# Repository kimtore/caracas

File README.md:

# Caracas

Caracas is an open source DIY car stereo system for the Toyota Avensis 2007, running on Raspberry Pi with custom hardware modifications.

[See pictures](http://imgur.com/a/6FCoq) of Caracas in action!

## Features

* Front panel with volume button and a 800x480 resistive touch panel with backlight control.
* Control music and other functions using steering wheel control buttons.
* Ignition key detection: hardware controlled power-on, software-controlled power-off.
* Plays music using MPD, through a HIFImeDIY Sabre DAC ES9023 to a class D 400W RMS amplifier.
* ISO 10487 connection for power and speaker connections.
* Custom-designed Raspberry Pi HAT for interfacing with the car hardware.
* SSD disk stores huge amounts of music.
* 4G Internet connection using car antenna.
* GPS module using car antenna.
* Custom interface with music controls, using Qt.
* ~~World-wide road navigation using Marble and OpenStreetMap.~~

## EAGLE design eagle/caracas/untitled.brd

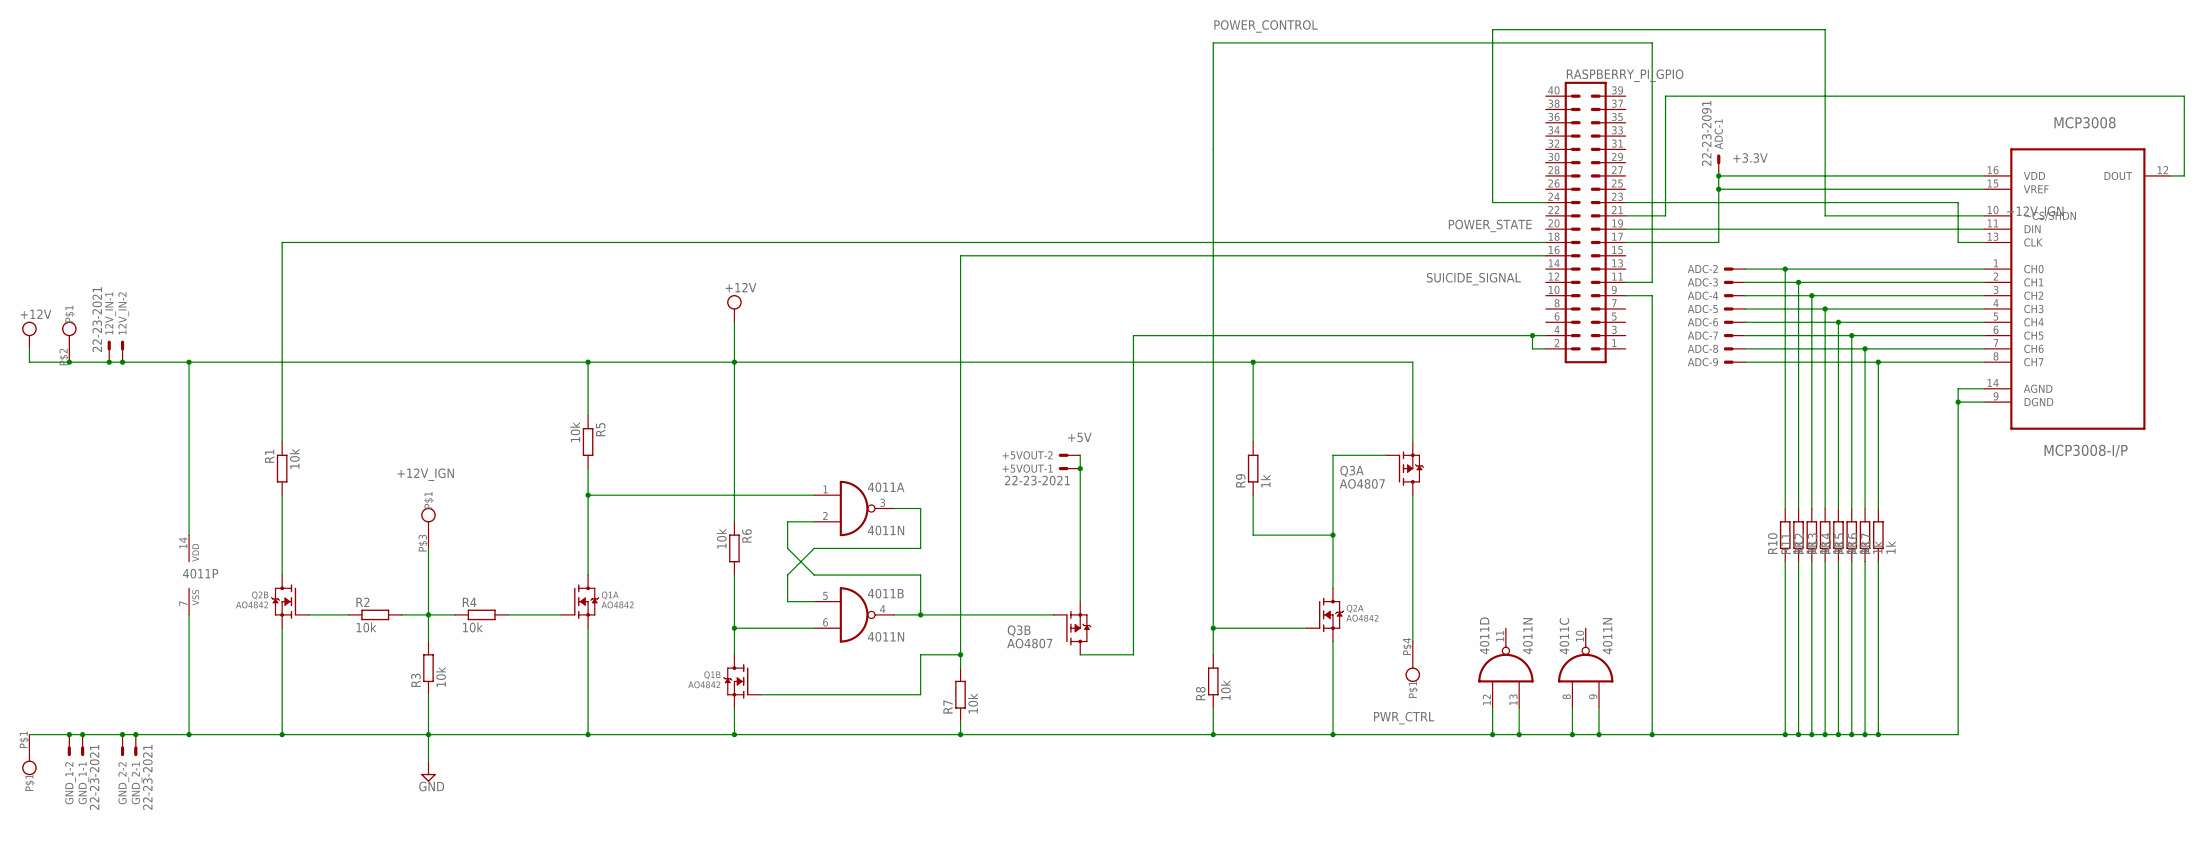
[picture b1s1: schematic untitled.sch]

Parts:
12V_IN: 22-23-2021
4011: 4011N; DIL14
+5VOUT: 22-23-2021
ADC: 22-23-2091
EXT: MKDS3
GND_1, GND_2: 22-23-2021
MCP3008: MCP3008-I/P; DIP254P762X432-16
Q1, Q2: AO4842; 8-SOIC
Q3: AO4807; 8-SOIC
R1, R2, R3, R4, R5, R6, R7, R8: 10k; 0207/10
R9, R10, R11, R12, R13, R14, R15, R16, R17: 1k; 0207/10
RASPBERRY_PI_GPIO: MA20-2

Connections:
+3.3V: ADC.1, MCP3008.15 (VREF), MCP3008.16 (VDD), RASPBERRY_PI_GPIO.17
+5V: +5VOUT.1, +5VOUT.2, Q3.P$1 (S)
+12V_IGN: EXT.P$3, R2.2, R3.2, R4.1
ANA_0: ADC.2, MCP3008.1 (CH0), R10.2
ANA_1: ADC.3, MCP3008.2 (CH1), R11.2
GND@BOTTOM: 4011.7 (VSS), 4011.8 (I0), 4011.9 (I1), 4011.12 (I0), 4011.13 (I1), EXT.P$1, GND_1.1, GND_1.2, GND_2.1, GND_2.2, MCP3008.9 (DGND), MCP3008.14 (AGND), Q1.P$1 (S), Q1.P$3 (S), Q2.P$1 (S), Q2.P$3 (S), R3.1, R7.1, R8.1, R10.1, R11.1, R12.1, R13.1, R14.1, R15.1, R16.1, R17.1, RASPBERRY_PI_GPIO.9
MOSFET_ON: 4011.2 (I1), 4011.4 (O), Q3.P$2 (G)
unnamed: 4011.3 (O), 4011.5 (I0)
unnamed: 4011.6 (I1), Q1.P$7 (D), Q1.P$8 (D), R6.2
unnamed: MCP3008.13 (CLK), RASPBERRY_PI_GPIO.23
unnamed: MCP3008.12 (DOUT), RASPBERRY_PI_GPIO.21
unnamed: MCP3008.11 (DIN), RASPBERRY_PI_GPIO.19
unnamed: ADC.4, MCP3008.3 (CH2), R12.2
unnamed: ADC.5, MCP3008.4 (CH3), R13.2
unnamed: ADC.6, MCP3008.5 (CH4), R14.2
unnamed: ADC.7, MCP3008.6 (CH5), R15.2
unnamed: 4011.1 (I0), Q1.P$5 (D), Q1.P$6 (D), R5.2
unnamed: Q1.P$4 (G), R4.2
unnamed: MCP3008.10 (~CS/SHDN), RASPBERRY_PI_GPIO.24
unnamed: ADC.8, MCP3008.7 (CH6), R16.2
unnamed: ADC.9, MCP3008.8 (CH7), R17.2
unnamed: Q3.P$7 (D), Q3.P$8 (D), RASPBERRY_PI_GPIO.2, RASPBERRY_PI_GPIO.4
unnamed: Q2.P$2 (G), R2.1
unnamed: Q2.P$7 (D), Q2.P$8 (D), R1.2
unnamed: Q2.P$5 (D), Q2.P$6 (D), Q3.P$4 (G), R9.1
POWER_CONTROL: Q2.P$4 (G), R8.2, RASPBERRY_PI_GPIO.11
POWER_STATE: R1.1, RASPBERRY_PI_GPIO.18
PWR_CTRL: EXT.P$4, Q3.P$5 (D), Q3.P$6 (D)
SUICIDE_SIGNAL: Q1.P$2 (G), R7.2, RASPBERRY_PI_GPIO.16
VCC: 12V_IN.1, 12V_IN.2, 4011.14 (VDD), EXT.P$2, Q3.P$3 (S), R5.1, R6.1, R9.2

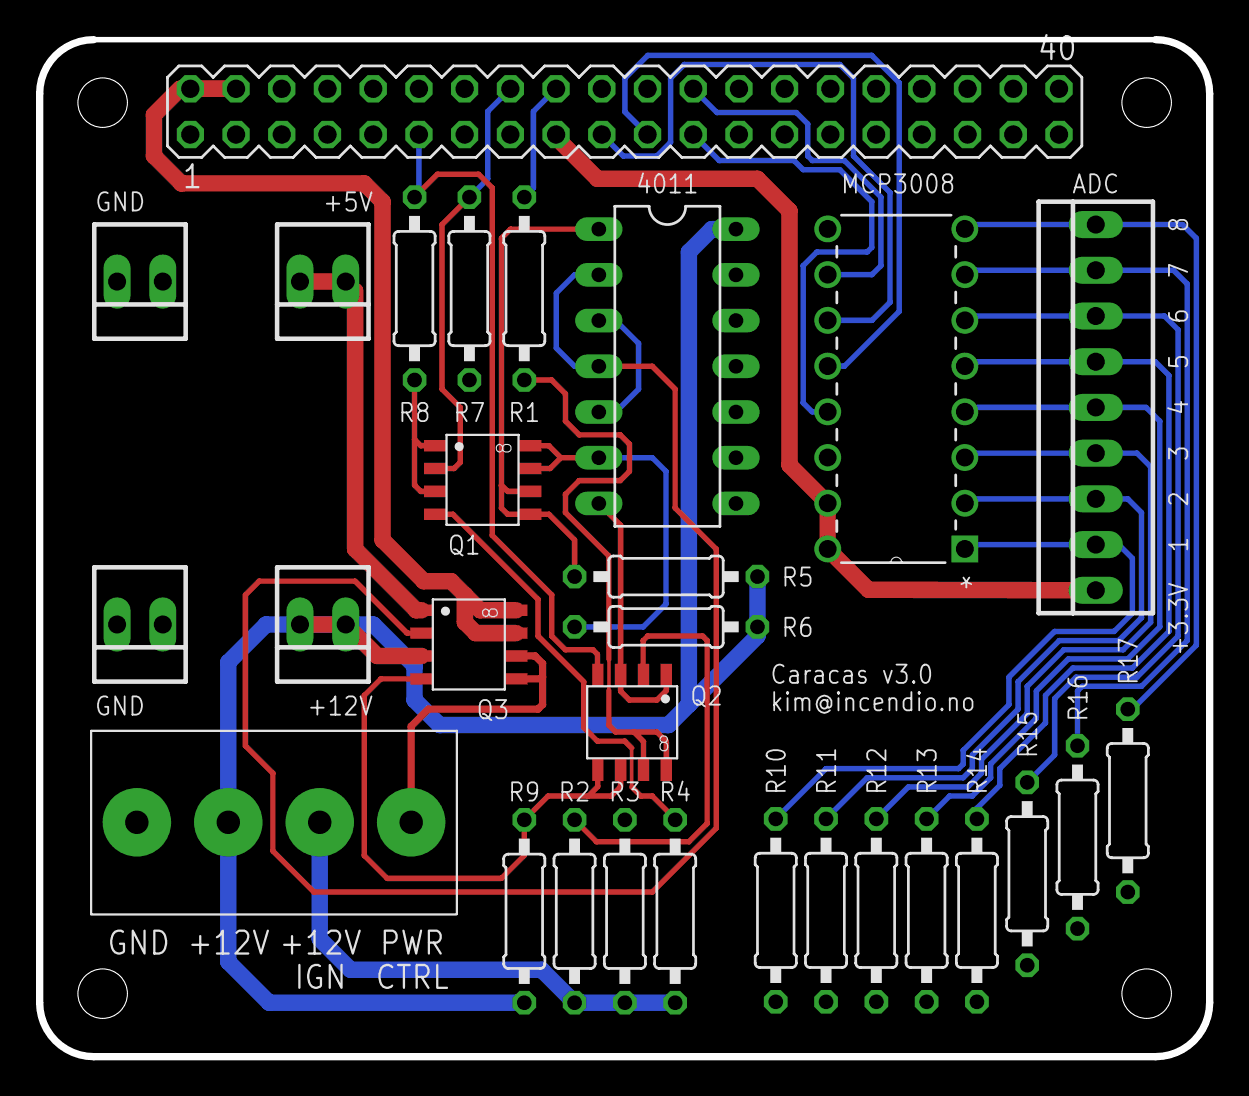
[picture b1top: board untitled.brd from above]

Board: 2 copper layers, 65.0 x 56.5 mm, 29 parts (0 on the bottom side), 30 nets.

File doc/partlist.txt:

Partlist

Exported from untitled.sch at 5/25/15 12:14 PM

EAGLE Version 6.5.0 Copyright (c) 1988-2013 CadSoft

Assembly variant: 

Part              Value          Device       Package           Library   Sheet

+5VOUT            22-23-2021     22-23-2021   22-23-2021        con-molex 1
12V_IN            22-23-2021     22-23-2021   22-23-2021        con-molex 1
4011              4011N          4011N        DIL14             40xx      1
ADC               22-23-2091     22-23-2091   22-23-2091        con-molex 1
EXT               MKDS3          MKDS3        MKDS3             caracas   1
GND_1             22-23-2021     22-23-2021   22-23-2021        con-molex 1
GND_2             22-23-2021     22-23-2021   22-23-2021        con-molex 1
MCP1              MCP3008-I/P    MCP3008-I/P  DIP254P762X432-16 mpc3008   1
Q1                AO4842         AO4842       8-SOIC            caracas   1
Q2                AO4842         AO4842       8-SOIC            caracas   1
Q3                AO4807         AO4807       8-SOIC            caracas   1
R1                10k            R-EU_0207/10 0207/10           rcl       1
R2                10k            R-EU_0207/10 0207/10           rcl       1
R3                10k            R-EU_0207/10 0207/10           rcl       1
R4                10k            R-EU_0207/10 0207/10           rcl       1
R5                10k            R-EU_0207/10 0207/10           rcl       1
R6                10k            R-EU_0207/10 0207/10           rcl       1
R7                10k            R-EU_0207/10 0207/10           rcl       1
R8                10k            R-EU_0207/10 0207/10           rcl       1
R9                1k             R-EU_0207/10 0207/10           rcl       1
R10               1k             R-EU_0207/10 0207/10           rcl       1
R11               1k             R-EU_0207/10 0207/10           rcl       1
RASPBERRY_PI_GPIO                MA20-2       MA20-2            con-lstb  1

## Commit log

2014-08-11 Let's call this an initial commit.
2014-08-11 Make zmq communication more meaningful.
2014-08-18 Add the python ZMQ utilities.
2014-08-18 Add some documentation.
2014-08-21 Add CAD files and Fritzing file.
2014-08-22 Update some CAD and fritzing drawings.
2014-08-28 Add WIP.
2014-08-29 Add Eagle schematics.
2014-09-16 Update Eagle project.
2014-09-16 Add more component data sheets.
2014-09-16 Ignore backup files.
2014-09-16 Update Eagle schematics.
2014-09-23 Add the CD2109 SATA connector datasheet.
2014-09-23 Add the CD2109 SATA connector to EAGLE library.
2014-09-23 EAGLE: draw SATA connector into schematics.
2014-09-23 Finished design?
2014-10-21 Save the board again.
2014-12-07 Document electronics and dimensions in Toyota Avensis 2008.
2014-12-07 Add 177x180x100mm case plans with makercase.com
2014-12-07 Move original Android project into subdirectory.
2014-12-07 Add Toyota wiring harness documentation.
2014-12-07 Update the case plans with holes and front panel.
2014-12-08 Add electronics link for transistors.
2014-12-08 Update case plans.
2014-12-13 Add Samsung S2 dimensions.
2014-12-13 Update caseplans with real dimensions of Samsung S2.
2014-12-16 WIP on electronics schematics.
2014-12-16 Add data sheet for MCP3008.
2014-12-16 Update case plans with 12mm thick material.
2014-12-16 WIP on electronics schema.
2014-12-17 More WIP on the electronics schematics, closing in...
2014-12-18 Schematic and board finished (at least R1)
2014-12-18 Add IRLZ44Z datasheet.
2014-12-18 Fixed a design bug
2014-12-18 Moved some android code.
2014-12-27 Fix the android project.
2014-12-27 Update case and panel dimensions, split into two documents, add demo PDF
2014-12-28 SPI clock in on pin 23, not pin 5
2014-12-29 Fixed errors in the electrical diagram.
2015-01-03 Add the first workings on a GPIO monitoring daemon.
2015-01-08 Start writing interface requirements.
2015-01-08 New case dimensions, and add exported DXF files.
2015-01-09 Discovered some things that does not work.
2015-01-09 Document voltage dividers.
2015-01-10 Case design modified again, this time using an Inkscape plugin.
2015-01-10 Schematics: replace CD4027N J/K flip-flop with 4011N nand gates.
2015-01-14 Remove obsolete component from electronics schematics. Clean up board paths.
2015-01-14 Add CD4001UBE datasheet.
2015-01-14 Add 1N5333BG datasheet.
2015-01-14 Remove CD4027BE datasheet.
2015-01-21 Use correct size for DC/DC converter, and compress size of board.
2015-01-21 Panel design v1.1.
2015-01-21 Move panel design into the rest of the case design.
2015-01-21 Remove old files.
2015-01-21 Revert "Remove old files."
    This reverts commit f4e2b1f7f905ac7efe4b1a62f424aaef31f10205.
2015-01-29 Update schematics again.
2015-01-29 Assign values to resistors.
2015-02-05 WIP schematics
2015-02-05 Document ADC value on voltage divider for steering controls.
2015-02-05 WIP electronics.
2015-02-08 Possibly last version of schematics.
2015-02-08 Add OshPark design rules file.
2015-02-08 Schematics adjusted once again.
2015-02-12 Switch to wiringPi library, rewrite rotary pin detection code.
2015-02-12 Implement rotary switch detection code.
2015-02-12 Add documentation and stub out MPC3008 SPI access.
2015-03-26 Add daemon 'suicided', shutting down system when ignition power disappears
2015-03-26 Use fork() in sigd
2015-03-26 Globalize ZeroMQ variables, drop the fork stuff
2015-03-26 Use interrupts for main loop instead of timing delay
2015-03-26 Add power state monitoring to sigdaemon
2015-03-26 Remove extraneous files
2015-03-26 Don't spam output with zeromq messages from sigdaemon
2015-03-26 Makeshift event daemon
2015-03-26 Add some init scripts
2015-03-26 ADB likes to assume that port 5555 is used by an emulator
2015-03-26 Clean up sigdaemon and add debouncing of switches.
2015-03-26 More
2015-03-27 Reset defaults, add install action to Makefile
2015-03-27 Update init scripts
2015-04-03 Refactor hardware board into a Raspberry PI B+ compatible HAT board
2015-04-04 Add Raspberry PI HAT board mechanical documentation
2015-04-04 More experimentation with the Android daemon
2015-04-04 Remove the Android daemon, not needed
2015-04-04 Commit some android build.props
2015-04-05 Add Raspberry PI GPIO image schematic
2015-04-05 Small board layout changes
2015-04-06 Document stereo cage physical dimensions required for hole drilling
2015-04-06 Add front panel exact dimensions
2015-04-11 Begin describing pin mapping
2015-04-11 Add transistor datasheet
2015-04-16 Update schematics again
2015-04-16 Power board: route power buses on top layer
2015-04-16 Final board v2.0
2015-04-16 Complete pin documentation
2015-04-16 Add 40-pin header datasheet
2015-05-06 Add a first version of a simple event generator
2015-05-06 Start coding pending shutdown code, WIP
2015-05-09 Add generated part list from Eagle
2015-05-10 Finish event simulator
2015-05-10 Wait for 15 seconds before attempting shutdown after ignition loss
2015-05-10 Add ADC test program 'wicked'
2015-05-10 Power state pin changed to 18 in board layout v2
2015-05-10 Bind sigd zmq publisher to all interfaces
2015-05-10 Android script must run on reboots
2015-05-10 Suicide pin should be GPIO 4
2015-05-14 Power board v2 does not work, start working on v3
2015-05-25 More schematics WIP
2015-05-25 Add powerboard v2 schematics and design snapshots
2015-05-26 Add SeeedStudio Eagle support files
2015-05-27 Complete rework of the PCB
2015-05-29 Remove a polygon
2015-05-29 Update board
2015-05-29 Add Gerber files for v3.0 board
2015-06-08 Implement SPI reading in sigdaemon
2015-06-11 Use Tasker instead of ADB when toggling screen on/off
2015-06-17 Hardware button fixes
2015-06-18 Adjust steering wheel pin values by actual measurements
2015-06-19 More parameter adjustments to sigd
2015-06-19 Android screen toggle replaced by ADB again
2015-06-27 Set up equalization using alsaequal
2015-06-27 Add sample mpd.conf
2015-06-27 Refactor Cardaemon
2015-06-27 Fix fuckup
2015-06-27 Updated equaliser
2015-06-28 Implement ZeroMQ proxy daemon
2015-06-28 Add webservice code, listens for battery events from Android
2015-06-28 Add support for Android battery state in car daemon
2015-06-28 Fixes on the last commits, upgrading to ZMQ 4.x
2015-06-28 Use syslog for all daemons
2015-06-28 Fix a couple of bugs, add screen support in webservice
2015-06-28 Switch off display and music when ignition power is lost
2015-06-29 Don't run tick loop unless there is a repeatable event fired
2015-06-29 Add script that reports network location to syslog
2015-06-29 Revert "Don't run tick loop unless there is a repeatable event fired"
    This reverts commit d6d9525e8a0139e77f94aeaeefae985b3121d511.
2015-07-01 Better syslog messages on battery events.
2015-07-08 Remove dead code
2015-07-08 Remove linebreaks from sigd's syslog messages
2015-07-08 Move MPD functionality out of card.py and into a separate C program
2015-07-08 Implement MPD UNPAUSE and clean up messages
2015-07-08 Reliable hibernation mode: only after power timeout
2015-07-08 Reduce power timeout to 2 seconds
2015-07-08 cmpd: faster reconnect to mpd
2015-07-08 Fix some screen on/off bugs
2015-07-08 Implement next/prev artist/album
2015-07-09 Support MPD change volume on older MPD versions
2015-07-09 Remove LOG_MAKEPRI from sigd.c
2015-07-14 Board pinout changing when adding the Adafruit Ultimate GPS HAT
2015-07-20 Swap rotary left and right pins
2015-07-20 Update mpd.conf for pulseaudio and normalization
2015-07-20 Add xinetd configuration
2015-07-20 Always switch on music when system boots, and switch screen and music off as fast as possible.
2015-07-20 Add gpslog.py, logging GPS coordinates to syslog every minute
2015-07-20 Small comparison fix
2015-07-21 Require that gpsd is started before gpslog
2015-07-21 Always keep the system powered on if /tmp/keepalive exists
2015-07-21 Add NTP configuration file with GPS and PPS source
2015-07-23 Don't use volume normalization
2015-07-28 Older MPD versions do not support mpd_run_toggle_pause, implementing it in cmpd instead
2015-07-29 ZeroMQ proxy daemon implementation moved from Python to C
2015-07-29 Fix Makefile for proxy
2015-07-29 Add additional reporting to GPSlog
2015-07-29 Workaround ZeroMQ socket startup and boot sequencing
2015-07-29 Add SMW coin sound
2015-07-29 Play the coin sound when system is placed in no-sleep mode
2015-10-03 Add Monit configuration file
2015-10-06 Add gpscat: simple Python program for replaying NMEA streams
2015-12-18 Use timeout when running external commands
2015-12-19 Document gpscat
2016-01-02 Add panel design file
2016-01-02 Make sure distance to left edge of panel is 44 mm
2016-01-02 Attempt an export of the panel CAD drawing to DXF format
2016-01-02 Add centered panel versions
2016-01-02 Add configuration files for operation with Xorg:
    * Awesome WM configuration
    * Basic icons for wbar
2016-01-28 Start coding a QT5 GUI
2016-01-28 Remove wbar from xinitrc
2016-01-28 Link against the correct Marble library
2016-01-28 Activate the Marble widget on GUI startup
2016-05-01 The GPIO utility changed location to /usr/bin
2016-05-01 sigd: separate ADC and other debug messages
2016-05-01 Improve debouncing code
2016-05-01 Ignore MCP3008 errors
2016-05-02 Switch out SystemV init scripts with systemd services and targets
2016-05-02 Remove the Android webservice code
2016-05-02 Restructure the sigdaemon/ directory
2016-05-02 Remove obsolete android script
2016-05-02 Add missing sigd and gitignore files
2016-05-02 Make sure 'make install' works on the utils
2016-05-03 Modify caracas.target to require multi-user.target
2016-05-03 Add basic Ansible task
2016-05-03 Fix a couple of systemd related Ansible bugs
2016-05-03 Simplify Ansible tags
2016-05-03 Enable 'make install' on caracas-gui
2016-05-03 Start styling the GUI application
2016-05-05 Create a daemon that controls the display brightness
2016-05-05 Make sure backlightctl is installed
2016-05-05 Allow fading from value to value in backlightctl
2016-05-06 Add a README file
2016-05-06 Deploy MPD configuration and blacklist the built-in soundcard
2016-05-06 Fix backlightd ZeroMQ interrupts
2016-05-08 Convert caracas daemon code to run on built-in display instead of Android mode
2016-05-08 Install card and gpslog when running make install daemons
2016-05-08 Make sure fading the screen works both directions
2016-05-08 Commit screenshots of version 3 of the Raspberry Pi HAT
2016-05-08 Clean up documentation directory
2016-05-08 Remove icon-size css override
2016-05-10 Add an MPD client to the GUI application
2016-05-10 Install needed packages to build the GUI application, and more
2016-05-11 Various GUI style fixes
2016-05-11 Remove syslog messages and signal handling from backlightd
2016-05-11 Fix install path for GUI
2016-05-11 Move title back to center
2016-05-11 Don't start GUI MPD client before GUI is ready
2016-05-11 X optimizations: prevent screen saver and mouse pointer
2016-05-12 Load PPS kernel module on boot
2016-05-12 Power-off after 15 minutes instead of 1 hour
2016-05-13 Add basic vehicle tracking to map screen
2016-05-13 GUI: optimize gps widgets for small screens
2016-05-13 Allow shutdown and reboot from the GUI
2016-05-13 System shutdown with systemctl is shutdown, not poweroff
2016-05-13 Do not kill a running reboot or shutdown
2016-05-14 Install logrotate
2016-05-14 Grant shutdown and reboot privileges to caracas user
2016-05-14 sigdaemon: don't ignore double states, interferes with ignition key event
2016-05-17 Improve car tracking and zooming
2016-05-17 Zoom to world by default
2016-05-20 Implement very basic searching and routing
2016-05-21 Improve ansible structure, making it possible to run locally
2016-05-21 Install Ansible in ansible recipe
2016-05-21 Tweak MPD parameters
2017-06-07 Clean up README and add image links.
